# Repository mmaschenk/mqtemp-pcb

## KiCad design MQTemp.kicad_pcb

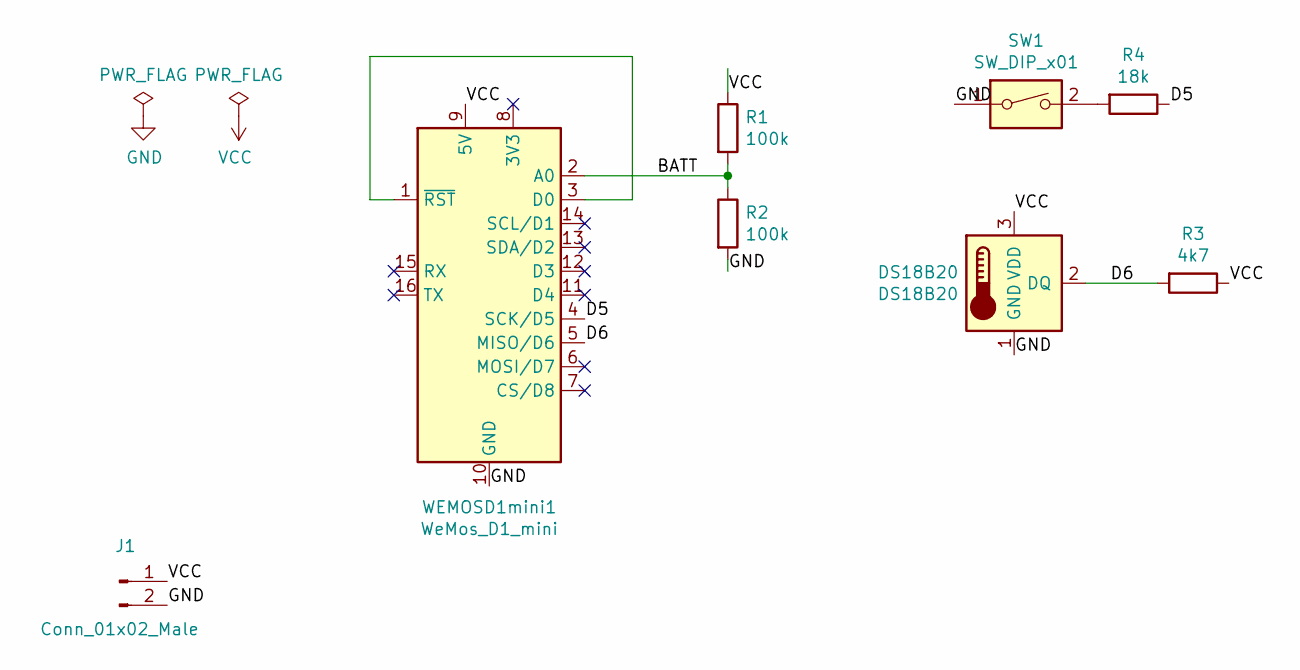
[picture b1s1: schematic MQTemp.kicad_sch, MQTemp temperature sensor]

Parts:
DS18B20: DS18B20; TO-92_Inline
J1: Conn_01x02_Male; PinHeader_1x02_P2.54mm_Vertical
R1, R2: 100k; R_Axial_DIN0207_L6.3mm_D2.5mm_P10.16mm_Horizontal
R3: 4k7; R_Axial_DIN0207_L6.3mm_D2.5mm_P10.16mm_Horizontal
R4: 18k; R_Axial_DIN0207_L6.3mm_D2.5mm_P10.16mm_Horizontal
SW1: SW_DIP_x01; SW_DIP_SPSTx01_Slide_9.78x4.72mm_W7.62mm_P2.54mm
WEMOSD1mini1: WeMos_D1_mini; WEMOS_D1_mini_light

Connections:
/BATT: R1.2, R2.1, WEMOSD1mini1.2 (A0)
/D5: R4.1, WEMOSD1mini1.4 (SCK/D5)
/D6: DS18B20.2 (DQ), R3.2, WEMOSD1mini1.5 (MISO/D6)
GND: DS18B20.1 (GND), J1.2, R2.2, SW1.1, WEMOSD1mini1.10 (GND)
unnamed: R4.2, SW1.2
unnamed: WEMOSD1mini1.1 (~RST), WEMOSD1mini1.3 (D0)
VCC: DS18B20.3 (VDD), J1.1, R1.1, R3.1, WEMOSD1mini1.9 (5V)

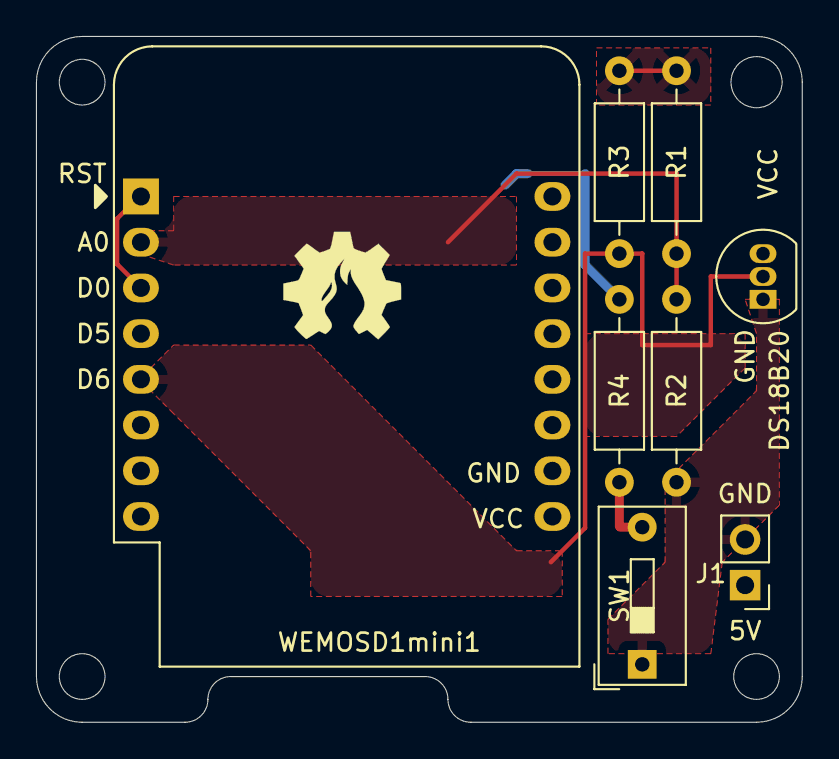
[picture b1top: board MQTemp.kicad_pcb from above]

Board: 2 copper layers, 42.5 x 38.1 mm, 10 parts (1 on the bottom side), 7 nets.

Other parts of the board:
GFACE: LOGO; mark-20mm
GOHL: LOGO; tudelft-10mm

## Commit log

2022-08-13 Added power connecter header holes
2022-08-13 Minor settings changes
2022-08-14 Added space for usb connector
2022-08-21 Connector placed and spacer rounded
2022-08-21 Smaller footprints. More compact design
2022-08-21 Version number up
2022-08-31 Added generated bom directory to git ignore
2022-09-04 uppercase license
2022-09-04 Changed input voltage to 3.3V
2022-09-06 Added filled zones
